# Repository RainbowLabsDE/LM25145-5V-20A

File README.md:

# LM25145-5V-20A
Buck Converter Board with LM25145 24V to 5V 20A

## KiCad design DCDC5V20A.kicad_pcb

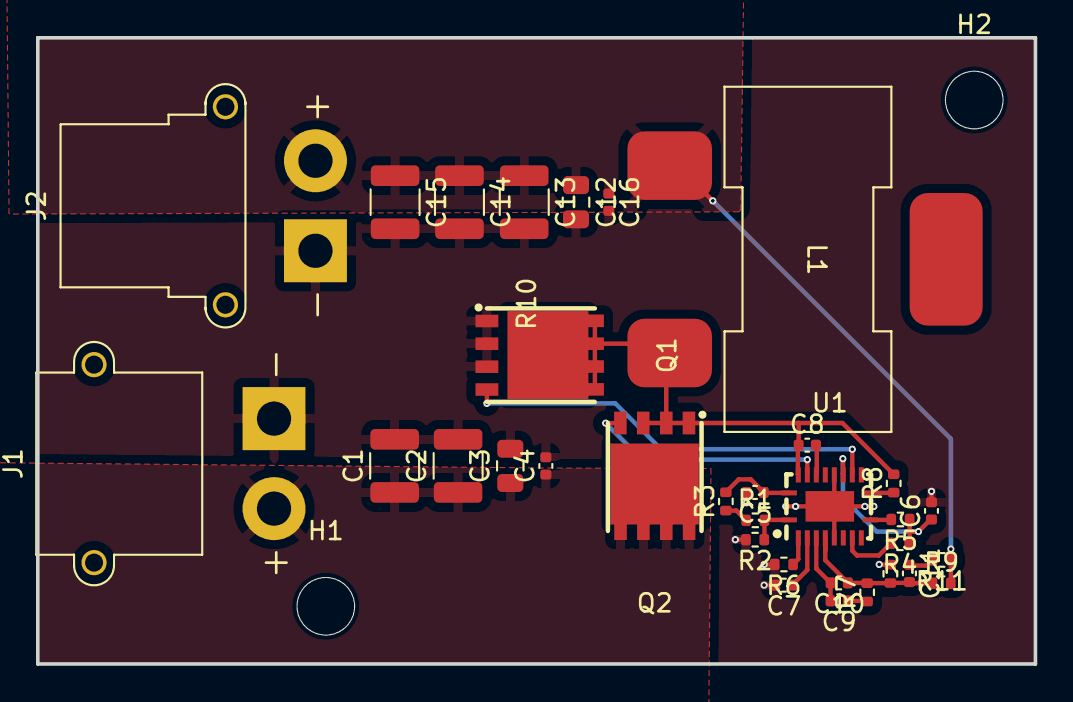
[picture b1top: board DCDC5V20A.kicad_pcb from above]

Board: 4 copper layers, 55.4 x 34.8 mm, 35 parts (0 on the bottom side), 19 nets.

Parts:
C1, C2: 4u7; C_1210_3225Metric
C3, C12: 1u; C_0805_2012Metric
C4, C5, C8, C16: 100n; C_0402_1005Metric
C6: 2n2; C_0402_1005Metric
C7: 56n; C_0402_1005Metric
C9: 5n6; C_0402_1005Metric
C10: 680p; C_0402_1005Metric
C11: 330p; C_0402_1005Metric
C13, C14, C15: 10u; C_1210_3225Metric
H1, H2: MountingHole; MountingHole_3.2mm_M3
J1: Conn_01x02_Socket; AMASS_XT30PW-M_1x02_P2.50mm_Horizontal
J2: Conn_01x02_Socket; AMASS_XT30PW-F_1x02_P2.50mm_Horizontal
L1: L; SER2009-122MLD
Q1, Q2: NMOS; VSON-CLIP-8_L5.0-W6.0-P1.27-BL
R1: 75k; R_0402_1005Metric
R2: 8k25; R_0402_1005Metric
R3: 2R1; R_0402_1005Metric
R4, R5: 20k; R_0402_1005Metric
R6: 30k1; R_0402_1005Metric
R7: 1k54; R_0402_1005Metric
R8: 536; R_0402_1005Metric
R9: 18k; R_0402_1005Metric
R10: 3k4; R_0402_1005Metric
R11: 232; R_0402_1005Metric
U1: VQFN-20_L4.5-W3.5-P0.50-BL-EP

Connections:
GND: C1.2, C2.2, C3.2, C4.2, C5.2, C6.2, C7.2, C12.2, C13.2, C14.2, C15.2, C16.2, J1.1, J2.1, Q1.3 (S), R2.2, R6.2, R10.1, U1.6 (AGND), U1.12 (PGND), U1.15 (EP), U1.21 (EP)
unnamed: C9.1, R7.1
unnamed: C11.1, R11.2
unnamed: C1.1, C2.1, C3.1, C4.1, J1.2, Q2.1 (D), R1.1, R3.1
unnamed: C12.1, C13.1, C14.1, C15.1, C16.1, J2.2, L1.1, R9.2, R11.1
unnamed: C8.1, L1.2, Q1.1 (D), Q2.3 (S), R8.2, U1.19 (SW)
unnamed: Q1.2 (G), U1.13 (LO)
unnamed: Q2.2 (G), U1.18 (HO)
unnamed: C8.2, U1.17 (BST)
unnamed: C9.2, C10.2, U1.4 (COMP)
unnamed: R1.2, R2.1, U1.1 (EN/UVLO)
unnamed: C10.1, C11.2, R7.2, R9.1, R10.2, U1.5 (FB)
unnamed: R8.1, U1.11 (ILIM)
unnamed: R5.2, U1.10 (PGOOD)
unnamed: R6.1, U1.2 (RT)
unnamed: C7.1, U1.3 (SS/TRK)
unnamed: R4.2, U1.8 (SYNCIN)
unnamed: C6.1, R4.1, R5.1, U1.14 (VCC)
unnamed: C5.1, R3.2, U1.20 (Vin)

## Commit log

2023-12-09 add schematic Fils
2024-01-25 edit layout
